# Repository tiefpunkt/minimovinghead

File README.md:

# Mini Moving Head

Design for a small moving head with a 3W RGB LED, controlled by DMX, and powered with an ESP8266.

## Firmware
Firmware is written using the ESP8266 Arduino integration.

Libraries used:
* [LXESP8266DMX](https://github.com/claudeheintz/LXESP8266DMX) for DMX input
* ESP8266 standard Servo library

## Electronics
Schematics are designed in KiCAD.

The LED driver design is based on [this design](http://www.tbideas.com/blog/build-an-arduino-shield-to-drive-high-power-rgb-led/) by TBIdeas.

Component Libraries:
* [ESP8266](https://github.com/jdunmire/kicad-ESP8266)

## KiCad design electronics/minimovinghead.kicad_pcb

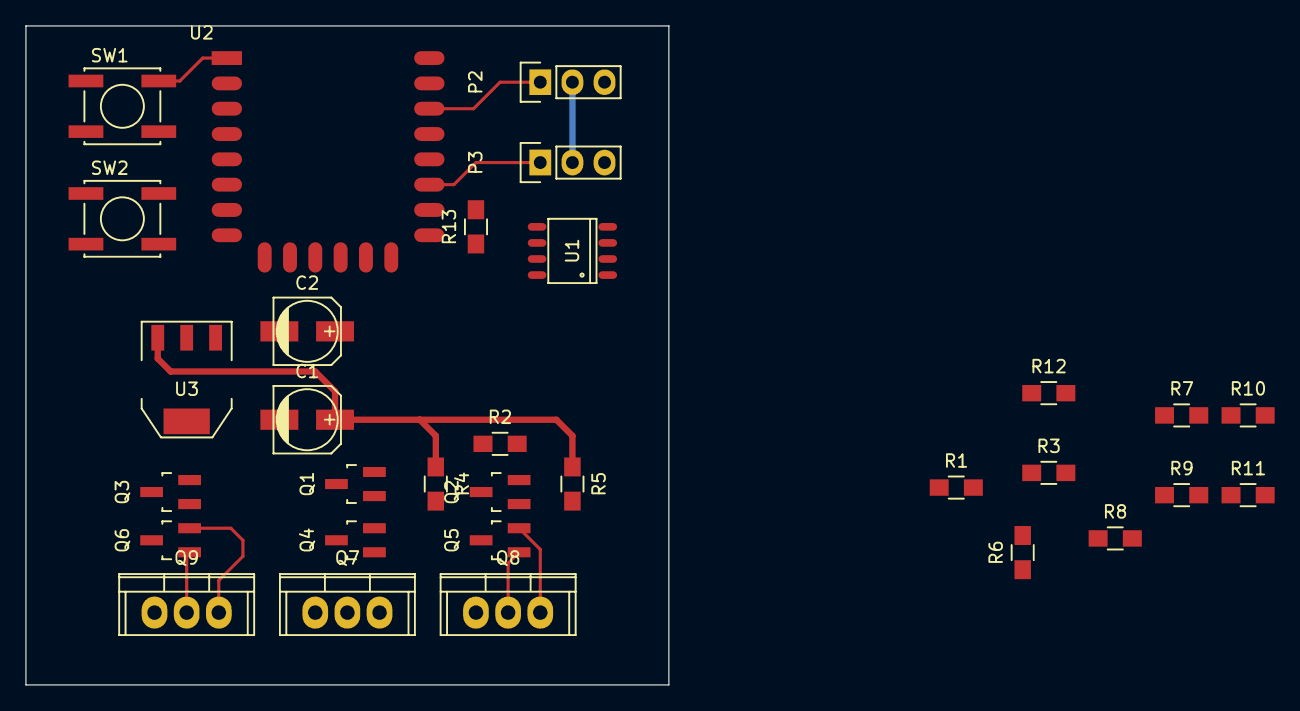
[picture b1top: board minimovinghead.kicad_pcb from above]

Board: 2 copper layers, 50.8 x 52.1 mm, 31 parts (0 on the bottom side), 22 nets.

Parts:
C1, C2: 10µ; c_elec_5x5.3
P2: Servo A; Pin_Header_Straight_1x03
P3: Servo B; Pin_Header_Straight_1x03
Q1, Q2, Q3, Q4, Q5, Q6: 2N3904; SOT-23_Handsoldering
Q7, Q8, Q9: BUZ71; TO-220
R1, R2, R3, R4, R5, R6, R10, R11, R12, R13: 10k; R_0805_HandSoldering
R7, R8, R9: 1.5; R_0805_HandSoldering
SW1, SW2: SW_PUSH; SW_SPST_EVPBF
U1: SN17576; SO-8
U2: ESP-12E
U3: TS 1117 BCW33; SOT-223

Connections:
+3V3: C2.1, R10.1, R11.1, R13.1, U1.8, U2.8, U3.1
+5V: C1.1, P2.2, P3.2, R4.1, R5.1, R6.1, U3.3
GND: C1.2, C2.2, P2.3, P3.3, Q1.3, Q2.3, Q3.3, Q4.3, Q5.3, Q6.3, R7.2, R8.2, R9.2, R12.2, SW1.2, SW2.2, U1.2, U1.3, U1.5, U2.15, U3.2
unnamed: P2.1, U2.20
unnamed: P3.1, U2.17
unnamed: Q1.1, Q4.1, Q7.2, R4.2
unnamed: Q1.2, R1.2
unnamed: Q2.1, Q5.1, Q8.2, R5.2
unnamed: Q2.2, R2.2
unnamed: Q3.1, Q6.1, Q9.2, R6.2
unnamed: Q3.2, R3.2
unnamed: Q4.2, Q7.3, R7.1
unnamed: Q5.2, Q8.3, R8.1
unnamed: Q6.2, Q9.3, R9.1
unnamed: R1.1, U2.5
unnamed: R2.1, U2.6
unnamed: R3.1, U2.7
unnamed: R10.2, SW1.1, U2.1
unnamed: R11.2, U2.3
unnamed: R12.1, U2.16
unnamed: R13.2, SW2.1, U2.18
unnamed: U1.1, U2.21

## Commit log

2016-02-07 added schematic
2016-08-01 working on the pcb
